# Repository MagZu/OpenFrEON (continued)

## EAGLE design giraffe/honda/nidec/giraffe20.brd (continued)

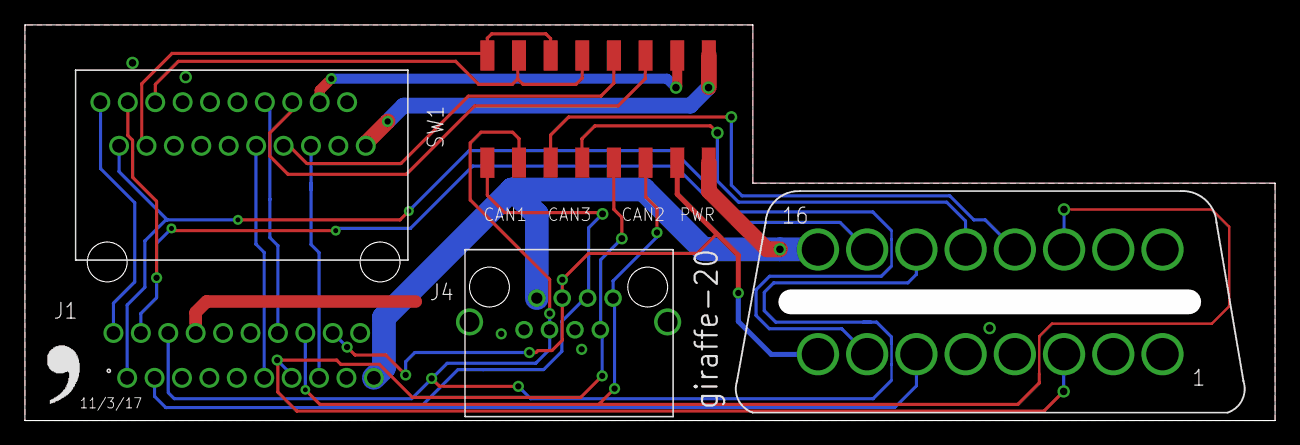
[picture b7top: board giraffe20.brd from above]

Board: 2 copper layers, 100.3 x 31.8 mm, 7 parts (1 on the bottom side), 21 nets.

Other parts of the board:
U$1: LOGO

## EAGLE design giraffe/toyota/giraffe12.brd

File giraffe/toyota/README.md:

Toyota giraffe
====

Get your panda deeper into your compatible Toyota vehicle

The switches
====

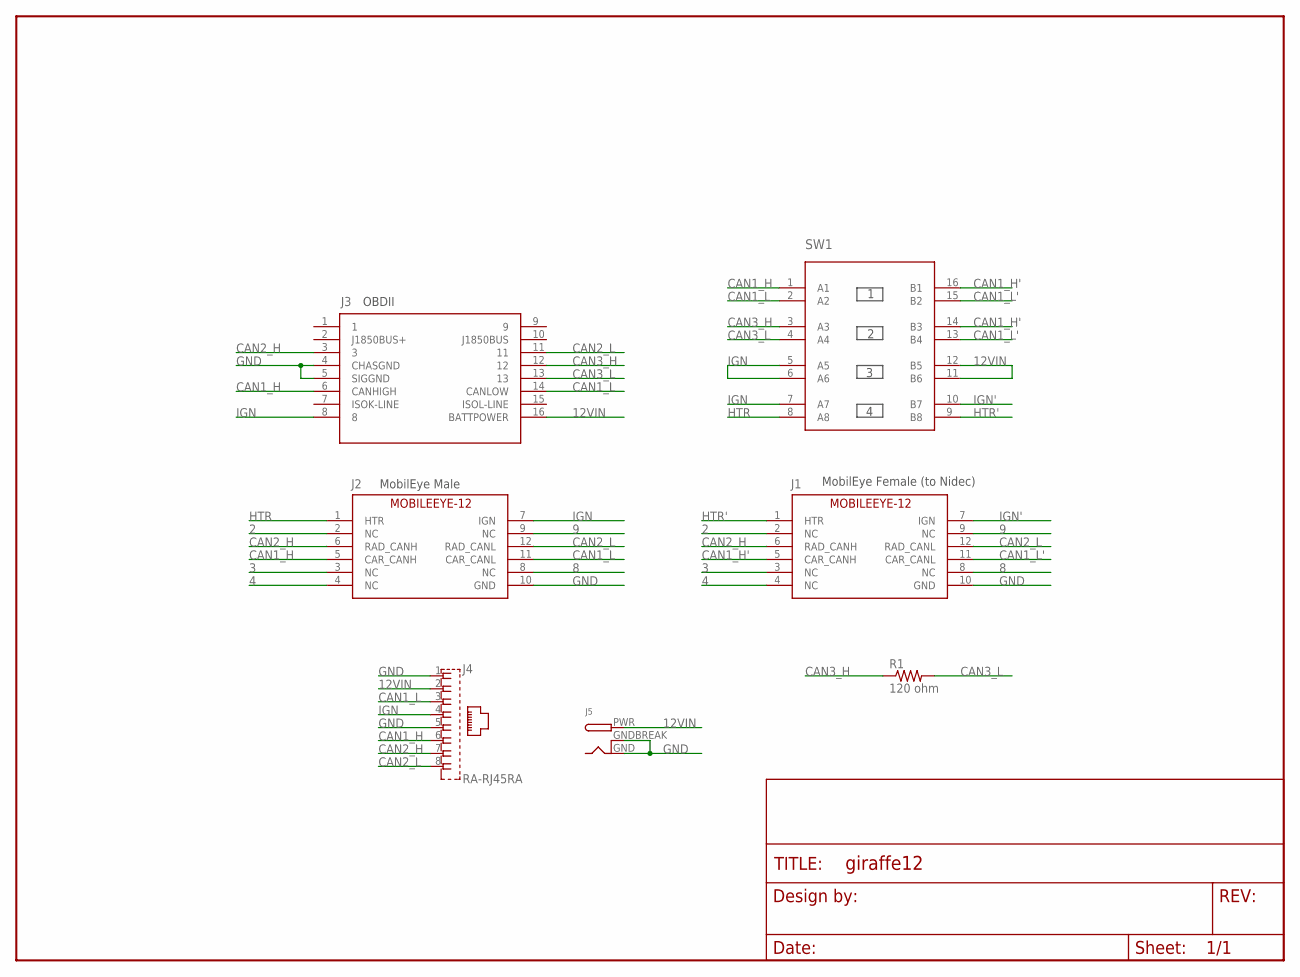
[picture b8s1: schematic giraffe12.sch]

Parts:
FRAME1: FRAME-LETTERNO_PACKAGE; DUMMY
J1: MOBILEEYE-12FEMALE; 2X6-TE-FEMALE
J2: MOBILEEYE-12MALE; 2X6-TE-RA
J3: OBDII-FEMALE-CUT; OBDII-FEMALE-MIDCUT
J4: RA-RJ45RA; RA-RJ45
J5: DCBARRELPTH; DCJACK_2MM_PTH
R1: 120 ohm; 0603-R
SW1: 4XDPSTSMT; 4-DPST

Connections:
2: J1.2 (NC), J2.2 (NC)
3: J1.3 (NC), J2.3 (NC)
4: J1.4 (NC), J2.4 (NC)
8: J1.8 (NC), J2.8 (NC)
9: J1.9 (NC), J2.9 (NC)
12VIN: J3.16 (BATTPOWER), J4.2, J5.PWR, SW1.11 (B6), SW1.12 (B5)
CAN1_H: J2.5 (CAR_CANH), J3.6 (CANHIGH), J4.6, SW1.1 (A1)
CAN1_H': J1.5 (CAR_CANH), SW1.14 (B3), SW1.16 (B1)
CAN1_L: J2.11 (CAR_CANL), J3.14 (CANLOW), J4.3, SW1.2 (A2)
CAN1_L': J1.11 (CAR_CANL), SW1.13 (B4), SW1.15 (B2)
CAN2_H: J1.6 (RAD_CANH), J2.6 (RAD_CANH), J3.3, J4.7
CAN2_L: J1.12 (RAD_CANL), J2.12 (RAD_CANL), J3.11, J4.8
CAN3_H: J3.12, R1.1, SW1.3 (A3)
CAN3_L: J3.13, R1.2, SW1.4 (A4)
GND: J1.10 (GND), J2.10 (GND), J3.4 (CHASGND), J3.5 (SIGGND), J4.1, J4.5, J5.GND, J5.GNDBREAK
HTR: J2.1 (HTR), SW1.8 (A8)
HTR': J1.1 (HTR), SW1.9 (B8)
IGN: J2.7 (IGN), J3.8, J4.4, SW1.5 (A5), SW1.6 (A6), SW1.7 (A7)
IGN': J1.7 (IGN), SW1.10 (B7)

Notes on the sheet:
OBDII
MobilEye Male
MobilEye Female (to Nidec)

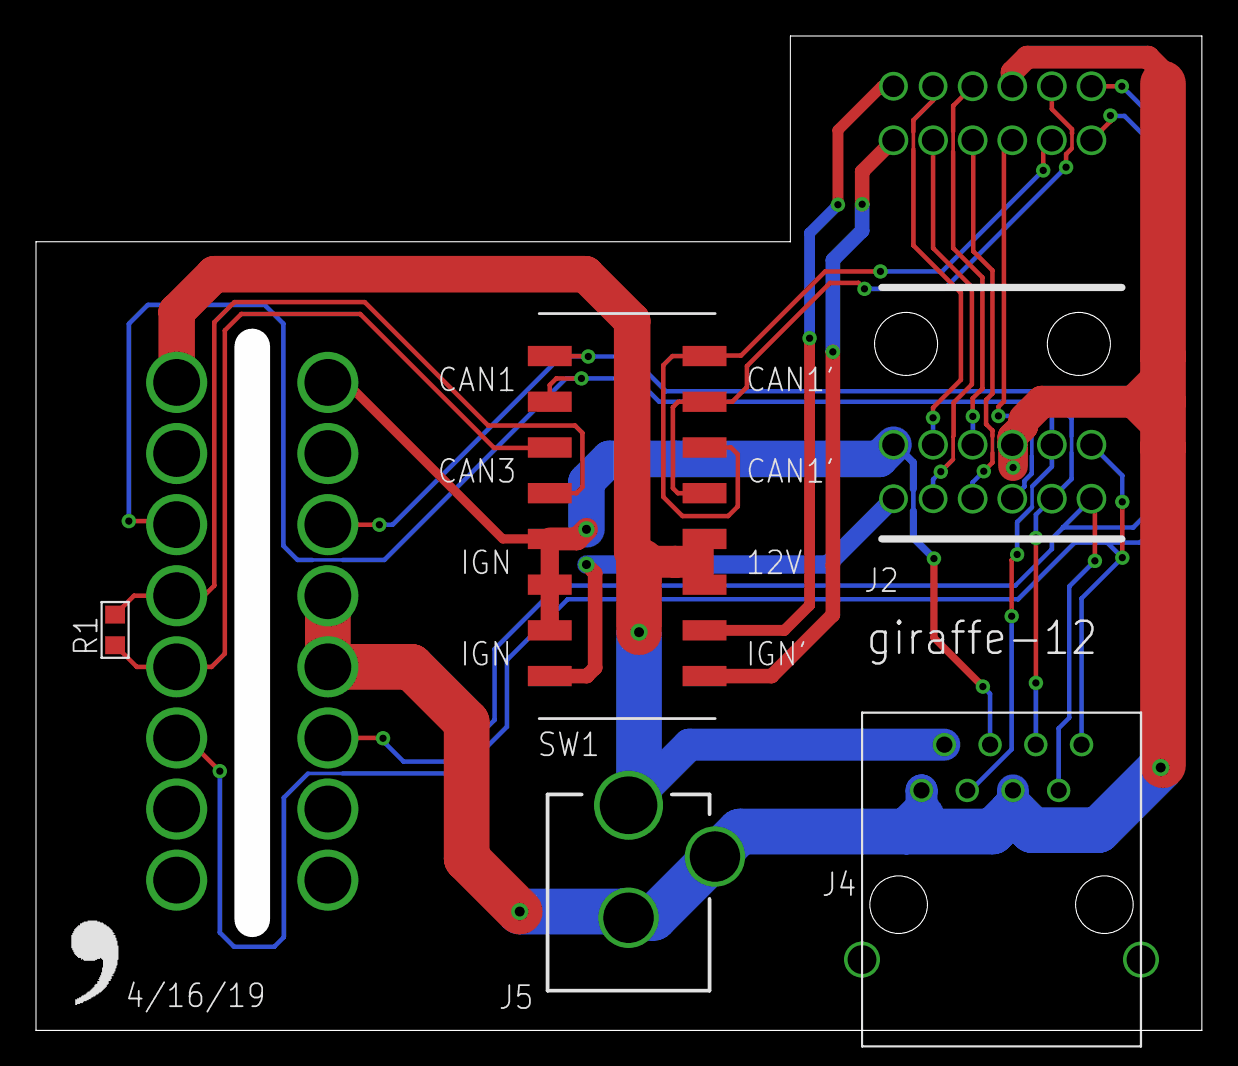
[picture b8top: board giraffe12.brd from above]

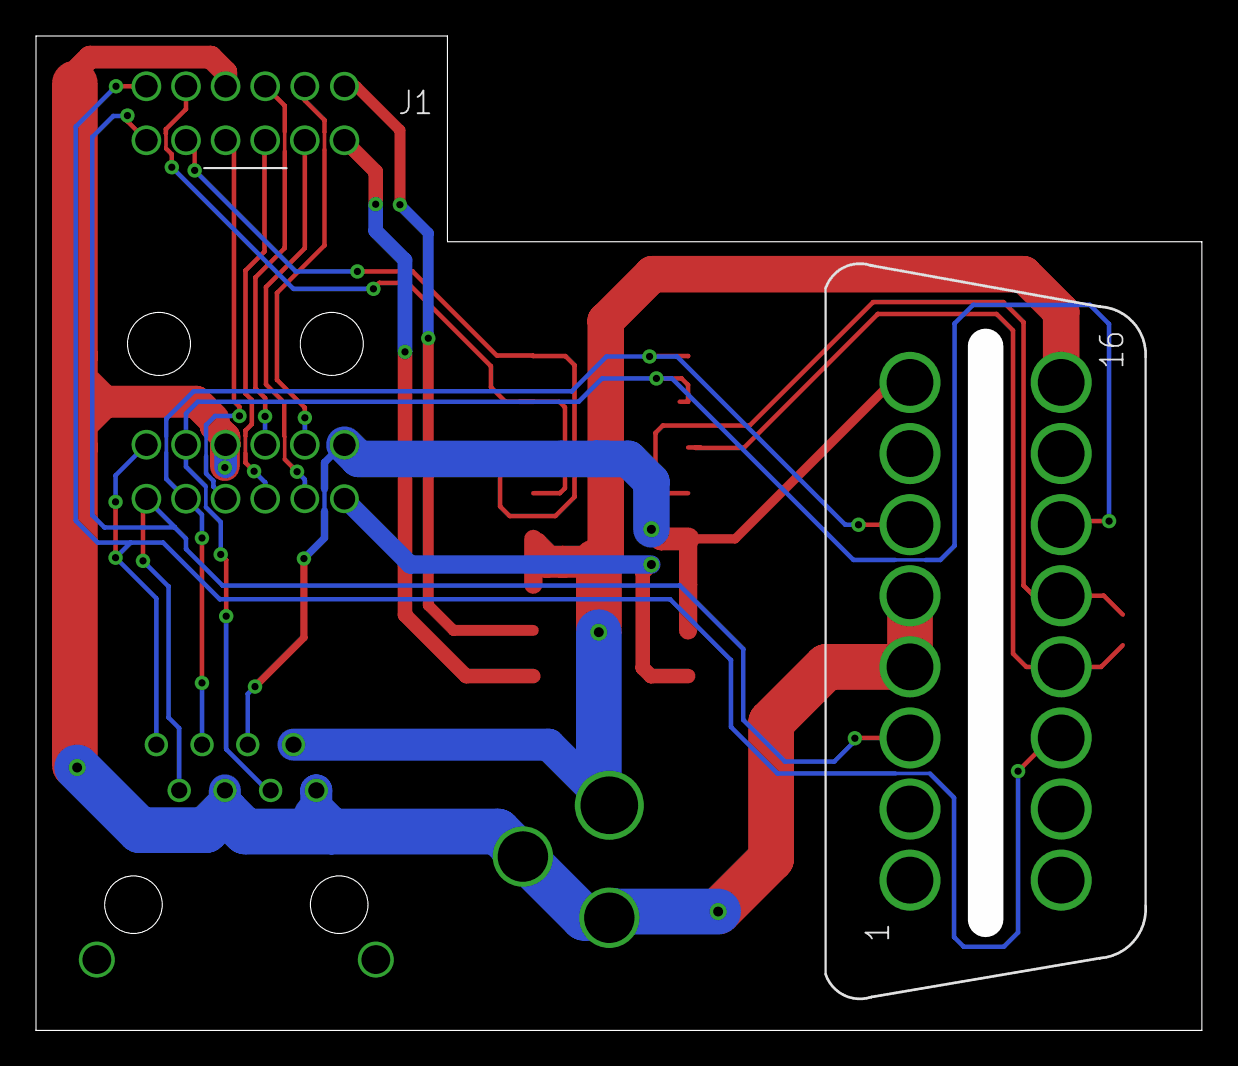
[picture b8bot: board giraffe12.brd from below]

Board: 2 copper layers, 64.8 x 55.2 mm, 9 parts (2 on the bottom side), 19 nets.

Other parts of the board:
U$1: LOGO

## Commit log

2019-06-25 调整打印文件
2019-06-30 提交挂钩
2019-07-01 添加底座
2019-07-03 添加油门和鹿的打印文件
2021-03-25 change folder names
    translate from chineese to english folder structure
2021-03-25 Update readme.txt
    Translate text to English
2021-04-15 Renamed files to english names
2021-04-15 Added Tesla recommended gopro mount
2021-04-15 Tinkla buddy nordic case readme added
2021-04-15 Tinkla Buddy Nordic Stl's uploaded
